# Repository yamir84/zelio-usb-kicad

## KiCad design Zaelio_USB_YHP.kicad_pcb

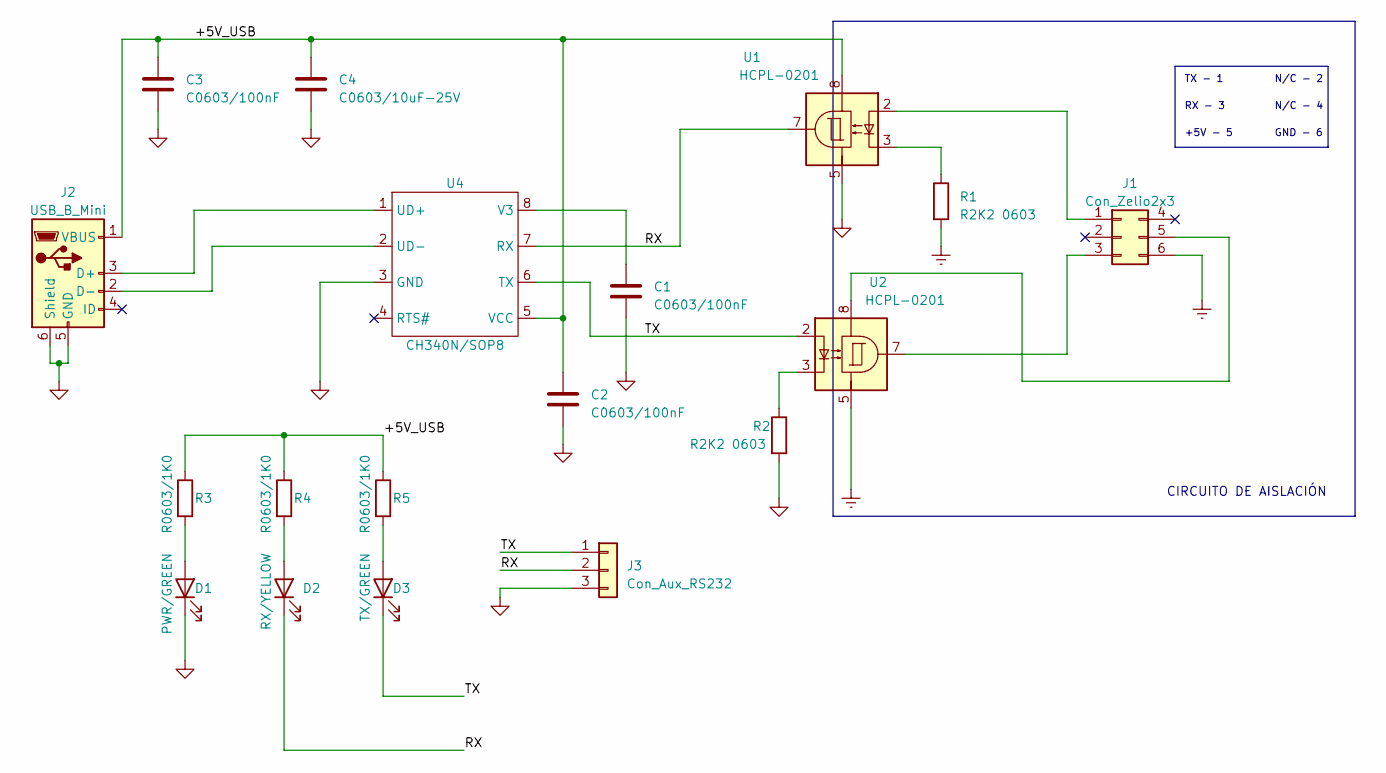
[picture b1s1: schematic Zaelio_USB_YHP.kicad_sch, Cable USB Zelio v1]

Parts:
C1, C2, C3: C0603/100nF; C_0603_1608Metric; LCSC C14663
C4: C0603/10uF-25V; C_0603_1608Metric; LCSC C96446
D1: PWR/GREEN; LED_0603_1608Metric; LCSC C72043
D2: RX/YELLOW; LED_0603_1608Metric; LCSC C72038
D3: TX/GREEN; LED_0603_1608Metric; LCSC C72043
J1: Con_Zelio2x3; PinHeader_2x03_P2.54mm_Horizontal
J2: USB_B_Mini; USB_Micro-B_GCT_USB3076-30-A; LCSC C319160
J3: Con_Aux_RS232; PinHeader_1x03_P2.54mm_Vertical
R1, R2: R2K2 0603; R_0603_1608Metric; LCSC C4190
R3, R4, R5: R0603/1K0; R_0603_1608Metric; LCSC C21190
U1, U2: HCPL-0201; SOIC-8_3.9x4.9mm_P1.27mm; LCSC C188694
U4: CH340N/SOP8; SO-8_3.9x4.9mm_P1.27mm; LCSC C506813

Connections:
/+5V_USB: C2.1, C3.1, C4.1, J2.1 (VBUS), R3.1, R4.1, R5.1, U1.8, U4.5 (VCC)
/RX: D2.1 (K), J3.2, U1.7, U4.7 (RX)
/TX: D3.1 (K), J3.1, U2.2, U4.6 (TX)
Earth: J1.6, R1.2, U2.5
GND: C1.2, C2.2, C3.2, C4.2, D1.1 (K), J2.5 (GND), J2.6 (Shield), J3.3, R2.2, U1.5, U4.3 (GND)
unnamed: D1.2 (A), R3.2
unnamed: D2.2 (A), R4.2
unnamed: D3.2 (A), R5.2
unnamed: J1.1, U1.2
unnamed: J1.3, U2.7
unnamed: J1.5, U2.8
unnamed: J2.3 (D+), U4.1 (UD+)
unnamed: J2.2 (D-), U4.2 (UD-)
unnamed: R1.1, U1.3
unnamed: R2.1, U2.3
unnamed: C1.1, U4.8 (V3)

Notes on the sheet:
GND - 6
N/C - 2
+5V - 5
TX - 1
N/C - 4
RX - 3
CIRCUITO DE AISLACIÓN

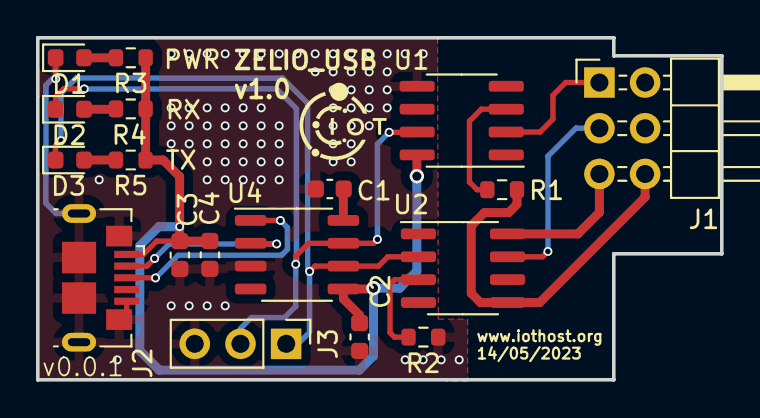
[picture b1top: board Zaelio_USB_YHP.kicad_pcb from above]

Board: 2 copper layers, 38.0 x 19.0 mm, 19 parts (0 on the bottom side), 16 nets.

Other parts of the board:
v0.0.1: zelio

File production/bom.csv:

Designator,Footprint,Quantity,Value,LCSC Part #
"C1, C2, C3",0603,3,C0603/100nF,C14663
C4,0603,1,C0603/10uF-25V,C96446
D1,0603,1,PWR/GREEN,C72043
D2,0603,1,RX/YELLOW,C72038
D3,0603,1,TX/GREEN,C72043
J2,USB_Micro-B_GCT_USB3076-30-A,1,USB_B_Mini,C319160
"R1, R2",0603,2,R2K2 0603,C4190
"R3, R4, R5",0603,3,R0603/1K0,C21190
"U1, U2",SOIC-8_3.9x4.9mm_P1.27mm,2,HCPL-0201,C188694
U4,SO-8_3.9x4.9mm_P1.27mm,1,CH340N/SOP8,C506813

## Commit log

2023-06-04 Zelio USB v1.0
